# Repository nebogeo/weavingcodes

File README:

Collected code for the weavingcodes/codingweaves project.

http://kairotic.org

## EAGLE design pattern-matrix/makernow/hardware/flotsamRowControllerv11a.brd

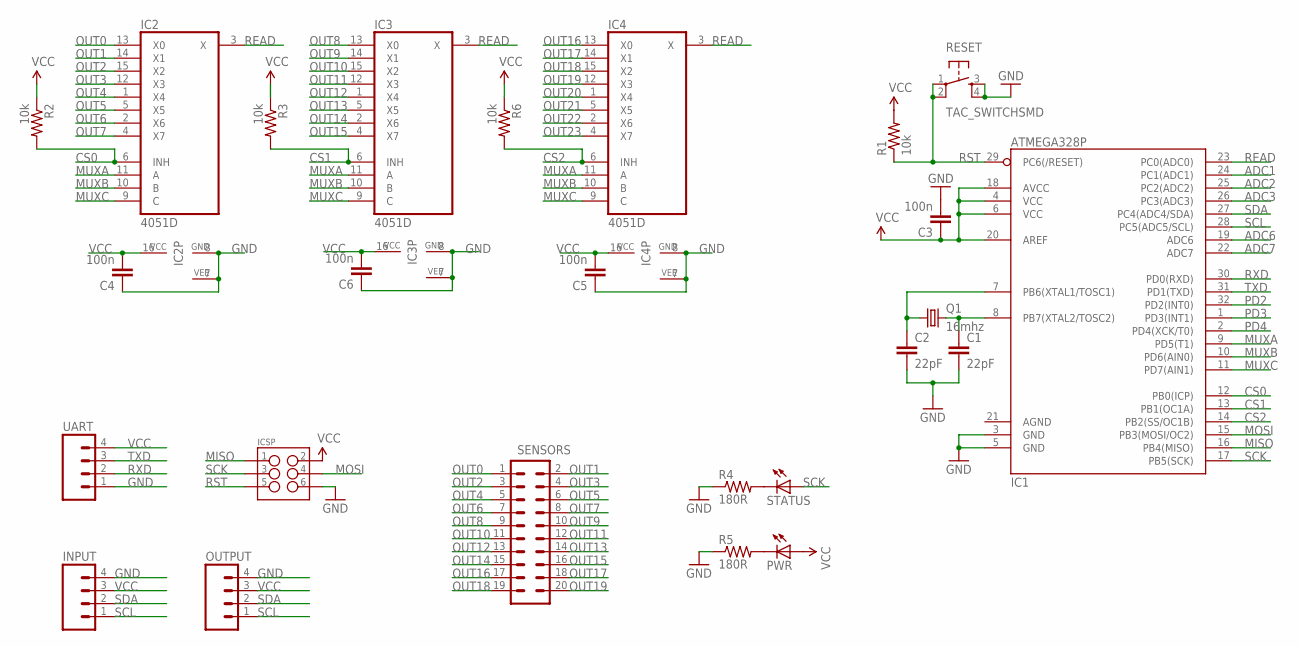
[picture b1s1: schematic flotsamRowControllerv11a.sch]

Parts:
C1, C2: 22pF; 0805
C3, C4, C5, C6: 100n; 0805
IC1: ATMEGA328P; TQFP32-08
IC2, IC3, IC4: 4051D; SO16
ICSP: M03X2FEMALE; 2X3
INPUT: M04LOCK; 1X04_LOCK
OUTPUT: M04LOCK; 1X04_LOCK
PWR: LEDSML0805; SML0805
Q1: 16mhz; HC49UP
R1, R2, R3, R6: 10k; 0805
R4, R5: 180R; 0805
RESET: TAC_SWITCHSMD; TACTILE-SWITCH-SMD
SENSORS: M10X22X10_LOCK; 2X10_LOCK
STATUS: LEDSML0805; SML0805
UART: M04LOCK; 1X04_LOCK

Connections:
ADC1: IC1.24 (PC1(ADC1))
ADC2: IC1.25 (PC2(ADC2))
ADC3: IC1.26 (PC3(ADC3))
ADC6: IC1.19 (ADC6)
ADC7: IC1.22 (ADC7)
CS0: IC1.12 (PB0(ICP)), IC2.6 (INH), R2.2
CS1: IC1.13 (PB1(OC1A)), IC3.6 (INH), R3.2
CS2: IC1.14 (PB2(SS/OC1B)), IC4.6 (INH), R6.2
GND: C1.2, C2.2, C3.2, C4.1, C5.1, C6.1, IC1.3 (GND), IC1.5 (GND), IC2.7 (VEE), IC2.8 (GND), IC3.7 (VEE), IC3.8 (GND), IC4.7 (VEE), IC4.8 (GND), ICSP.6, INPUT.4, OUTPUT.4, R4.1, R5.1, RESET.3, RESET.4, UART.1
MISO: IC1.16 (PB4(MISO)), ICSP.1
MOSI: IC1.15 (PB3(MOSI/OC2)), ICSP.4
MUXA: IC1.9 (PD5(T1)), IC2.11 (A), IC3.11 (A), IC4.11 (A)
MUXB: IC1.10 (PD6(AIN0)), IC2.10 (B), IC3.10 (B), IC4.10 (B)
MUXC: IC1.11 (PD7(AIN1)), IC2.9 (C), IC3.9 (C), IC4.9 (C)
unnamed: C1.1, IC1.8 (PB7(XTAL2/TOSC2)), Q1.2
unnamed: C2.1, IC1.7 (PB6(XTAL1/TOSC1)), Q1.1
unnamed: PWR.C, R5.2
unnamed: R4.2, STATUS.C
OUT0: IC2.13 (X0), SENSORS.1
OUT1: IC2.14 (X1), SENSORS.2
OUT2: IC2.15 (X2), SENSORS.3
OUT3: IC2.12 (X3), SENSORS.4
OUT4: IC2.1 (X4), SENSORS.5
OUT5: IC2.5 (X5), SENSORS.6
OUT6: IC2.2 (X6), SENSORS.7
OUT7: IC2.4 (X7), SENSORS.8
OUT8: IC3.13 (X0), SENSORS.9
OUT9: IC3.14 (X1), SENSORS.10
OUT10: IC3.15 (X2), SENSORS.11
OUT11: IC3.12 (X3), SENSORS.12
OUT12: IC3.1 (X4), SENSORS.13
OUT13: IC3.5 (X5), SENSORS.14
OUT14: IC3.2 (X6), SENSORS.15
OUT15: IC3.4 (X7), SENSORS.16
OUT16: IC4.13 (X0), SENSORS.17
OUT17: IC4.14 (X1), SENSORS.18
OUT18: IC4.15 (X2), SENSORS.19
OUT19: IC4.12 (X3), SENSORS.20
OUT20: IC4.1 (X4)
OUT21: IC4.5 (X5)
OUT22: IC4.2 (X6)
OUT23: IC4.4 (X7)
PD2: IC1.32 (PD2(INT0))
PD3: IC1.1 (PD3(INT1))
PD4: IC1.2 (PD4(XCK/T0))
READ: IC1.23 (PC0(ADC0)), IC2.3 (X), IC3.3 (X), IC4.3 (X)
RST: IC1.29 (PC6(/RESET)), ICSP.5, R1.1, RESET.1, RESET.2
RXD: IC1.30 (PD0(RXD)), UART.2
SCK: IC1.17 (PB5(SCK)), ICSP.3, STATUS.A
SCL: IC1.28 (PC5(ADC5/SCL)), INPUT.1, OUTPUT.1
SDA: IC1.27 (PC4(ADC4/SDA)), INPUT.2, OUTPUT.2
TXD: IC1.31 (PD1(TXD)), UART.3
VCC: C3.1, C4.2, C5.2, C6.2, IC1.4 (VCC), IC1.6 (VCC), IC1.18 (AVCC), IC1.20 (AREF), IC2.16 (VCC), IC3.16 (VCC), IC4.16 (VCC), ICSP.2, INPUT.3, OUTPUT.3, PWR.A, R1.2, R2.1, R3.1, R6.1, UART.4

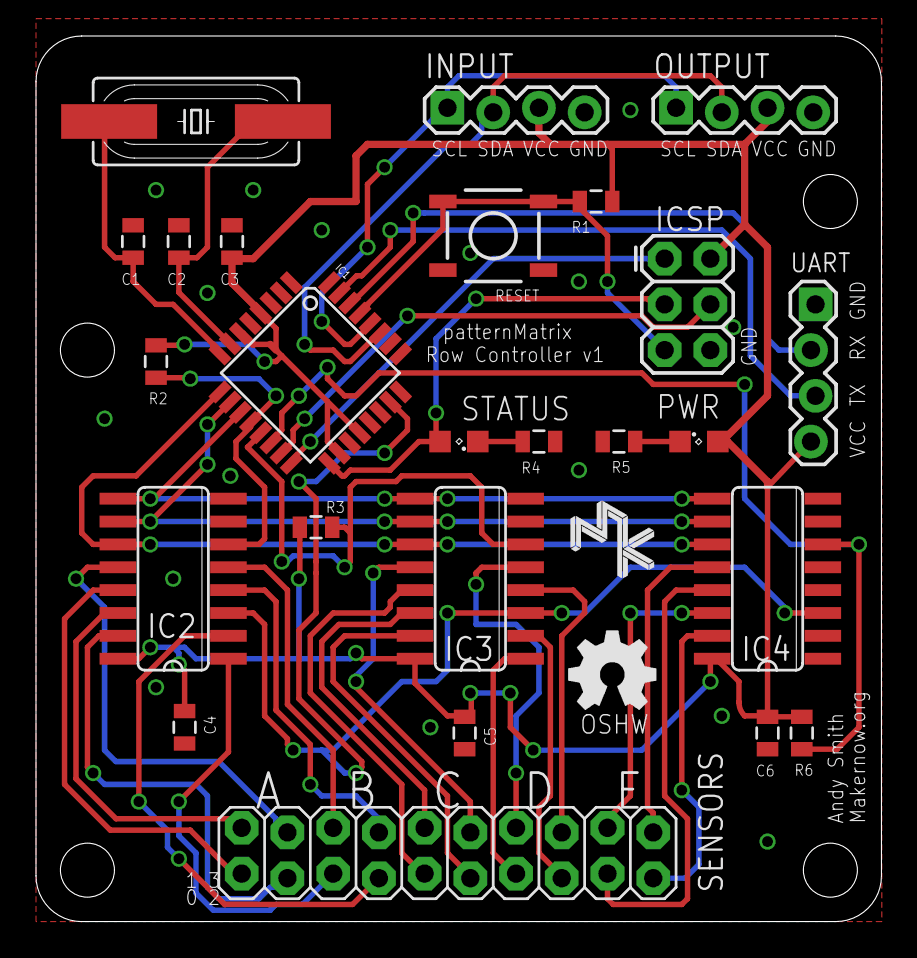
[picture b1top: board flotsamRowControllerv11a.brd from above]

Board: 2 copper layers, 47.0 x 49.2 mm, 27 parts (0 on the bottom side), 41 nets.

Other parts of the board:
U$1: MK_5MM
U$2: OSHW_5MM

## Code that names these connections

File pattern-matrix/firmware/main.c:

// Copyright (C) 2015 Dave Griffiths
//
// This program is free software; you can redistribute it and/or modify
// it under the terms of the GNU General Public License as published by
// the Free Software Foundation; either version 2 of the License, or
// (at your option) any later version.
//
// This program is distributed in the hope that it will be useful,
// but WITHOUT ANY WARRANTY; without even the implied warranty of
// MERCHANTABILITY or FITNESS FOR A PARTICULAR PURPOSE.  See the
// GNU General Public License for more details.
//
// You should have received a copy of the GNU General Public License
// along with this program; if not, write to the Free Software
// Foundation, Inc., 59 Temple Place - Suite 330, Boston, MA 02111-1307, USA.

// pattern matrix avr firmware
// reads the sensor data and makes it accessible to i2c devices

#include <avr/io.h>
#include <util/delay.h>
#include <stdlib.h>
#include <avr/interrupt.h>

#include "I2C_slave.h"

// buffer used to convert integer to string
char buffer[3];

#define LED PB0

#define PIN_READ PC0
#define PIN_MUXA PD5
#define PIN_MUXB PD6
#define PIN_MUXC PD7
#define PIN_CS0 PB0
#define PIN_CS1 PB1
#define PIN_CS2 PB2
#define PIN_STATUS PB5

//#define SINGLE_SENSOR
#define I2C_ID 0x36

// 35
// 33
// 34
// 32
// 36

void set_led_state(unsigned char s)
{
    if (s) PORTB|=_BV(PIN_STATUS);
    else PORTB&=~_BV(PIN_STATUS);
}

void outputb(unsigned int pin, unsigned char s)
{
    if (s) PORTB|=_BV(pin);
    else PORTB&=~_BV(pin);
}

void outputd(unsigned int pin, unsigned char s)
{
    if (s) PORTD|=_BV(pin);
    else PORTD&=~_BV(pin);
}

void index_sensor(unsigned int i) {
  unsigned int bank=i/8;
  unsigned int sensor=i%8;

  PORTD=((sensor&0x07)<<5);

  // set bits
  PORTB|=0x07;
  if (bank==0) outputb(PIN_CS0, 0);
  else if (bank==1) outputb(PIN_CS1, 0);
  else outputb(PIN_CS2, 0);
}

#define cbi(sfr, bit) (_SFR_BYTE(sfr) &= ~_BV(bit))

int main(void){
  	I2C_init(I2C_ID<<1); // initalize as slave with address 0x32

	// allow interrupts
        sei();

        // setup outputs
        DDRB = 0x00;
        DDRB |= _BV( PIN_STATUS );
        DDRB |= _BV( PIN_CS0 );
        DDRB |= _BV( PIN_CS1 );
        DDRB |= _BV( PIN_CS2 );

        DDRD = 0x00;
        DDRD |= _BV( PIN_MUXA );
        DDRD |= _BV( PIN_MUXB );
        DDRD |= _BV( PIN_MUXC );

        DDRC = 0x00;

        outputd(PIN_MUXA, 0);
        outputd(PIN_MUXB, 0);
        outputd(PIN_MUXC, 0);
        outputb(PIN_CS0, 0);
        outputb(PIN_CS1, 1);
        outputb(PIN_CS2, 1);

        for (int i=0; i<0xFF; i++) {
          i2cbuffer[i]=99;
        }

        int sensor = 1;
        int i2c_index = 0;

	while(1) {

#ifdef SINGLE_SENSOR

          _delay_ms(500);
          outputb(PIN_STATUS, 0);
          PORTD=((sensor&0x07)<<5);
          _delay_ms(100);
          if (PINC&_BV(PIN_READ)) {
            if (i2cbuffer[sensor]==1) outputb(PIN_STATUS, 1);
            i2cbuffer[sensor]=0;
          } else {
            if (i2cbuffer[sensor]==0) outputb(PIN_STATUS, 1);
            i2cbuffer[sensor]=1;
          }

          sensor++;
          if (sensor>4) sensor=0;

#else // 4 sensors

          _delay_ms(50);
          outputb(PIN_STATUS, 0);

          index_sensor(sensor);

          _delay_ms(10);
          if (PINC&_BV(PIN_READ)) {
            if (i2cbuffer[i2c_index]==1) outputb(PIN_STATUS, 1);
            i2cbuffer[i2c_index]=0;
          } else {
            if (i2cbuffer[i2c_index]==0) outputb(PIN_STATUS, 1);
            i2cbuffer[i2c_index]=1;
          }

          i2c_index++;
          sensor++;
          if (sensor>20) {
            sensor=0;
            i2c_index=0;
          }

#endif


	}

	return 0;
}

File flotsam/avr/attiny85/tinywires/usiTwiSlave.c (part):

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#  define DDR_USI             DDRB
#  define PORT_USI            PORTB
#  define PIN_USI             PINB
#  define PORT_USI_SDA        PB5
#  define PORT_USI_SCL        PB7
#  define PIN_USI_SDA         PINB5
#  define PIN_USI_SCL         PINB7
#  define USI_START_COND_INT  USISIF
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#  define DDR_USI             DDRB
#  define PORT_USI            PORTB
#  define PIN_USI             PINB
#  define PORT_USI_SDA        PB0
#  define PORT_USI_SCL        PB2
#  define PIN_USI_SDA         PINB0
#  define PIN_USI_SCL         PINB2
#  define USI_START_COND_INT  USISIF
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#  define DDR_USI             DDRB
#  define PORT_USI            PORTB
#  define PIN_USI             PINB
#  define PORT_USI_SDA        PB0
#  define PORT_USI_SCL        PB2
#  define PIN_USI_SDA         PINB0
#  define PIN_USI_SCL         PINB2
#  define USI_START_COND_INT  USISIF
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#  define DDR_USI             DDRB
#  define PORT_USI            PORTB
#  define PIN_USI             PINB
#  define PORT_USI_SDA        PB0
#  define PORT_USI_SCL        PB2
#  define PIN_USI_SDA         PINB0
#  define PIN_USI_SCL         PINB2
#  define USI_START_COND_INT  USISIF
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ISR( USI_START_VECTOR )
{

    PORTB|=_BV(PB3);


  /*
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
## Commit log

2014-10-17 added readme
2014-10-17 fixes for possible demo
2014-10-27 added online version
2014-10-27 added comments
2014-11-06 meander
2014-11-06 missing files
2014-11-12 better lsystem and stuff for flotsam
2014-11-25 added attiny85 code
2014-11-25 shifting stuff
2014-11-25 added atmega code
2014-11-25 removed cruft
2014-11-25 tidy
2014-11-26 rpi -> atmega works!
2014-11-26 attiny forgotten bits
2014-11-27 fixed reading -> pi
2014-12-28 added tablet weaving/livecoding sketch
2014-12-29 tablet weaving stuff
2015-01-02 added card viz
2015-01-02 links to source
2015-01-04 straight threads added to tablet
2015-02-12 added pattern matrix stuff
2015-02-12 gpio/osc/jellyfish comms
2015-02-27 tablet enlargement
2015-04-12 stuff for pattern matrix hardware
2015-04-12 sorting out pattern matrix code
2015-04-13 added python i2c code
2015-04-13 structure pygame hack
2015-04-17 firmware updated
2015-04-19 multisensor version added
2015-04-19 new wwloomsim
2015-04-19 added pattern cascade driver
2015-04-19 driver updates, untested
2015-04-19 temp
2015-04-22 colour and weave experiment, broken
2015-05-04 multiyarn and refactor
2015-05-04 double loom
2015-05-07 munich day 2
2015-05-07 draft modulo probs fixed
2015-05-07 selvedge smoothing
2015-05-07 final fiddly bits, thursday munich
2015-05-08 stuff from munich friday
2015-05-11 tidal residues
2015-05-11 types
2015-05-11 work not in progress
2015-05-11 lasercuttings etc
2015-06-02 added sound thingy for miners court
2015-06-02 miners court bits
2015-06-09 added thread tex
2015-06-09 added new colour seqs
2015-06-15 AIR/sheffield changes
2015-06-15 added missing munich files
2015-07-08 stuff for installations...
2015-07-20 added qt interface
2015-07-20 styling and adding colour
2015-07-20 connected up colours
2015-07-20 added livecoding editor
2015-07-21 paths fixes for osx
2015-07-21 added notes etc
2015-07-21 install fiddling
2015-07-21 start up state better
2015-07-21 mac install messing
2015-07-21 fixed warp draft addr
2015-10-15 dabblings with purescript
2015-10-19 further attempts at porting
2015-10-22 start of diagrams support
2015-10-27 dance weaving
2015-10-31 toothpaste added
2015-11-08 toothpaste updates
2015-11-23 added colour codes to dyadic
2015-11-23 missing images
2015-11-23 default loom to tabby weave
2016-01-25 added colour and setup commands to the tablet sim language
2016-01-25 colour flip
2016-01-25 added images
2017-05-14 mainly changes for munich installation, penelope project
2018-10-31 changes for new penelope version
2018-11-01 added thread texture

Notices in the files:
parts and their libraries:
SparkFun-Connectors: Licensing: Creative Commons ShareAlike 4.0 International - https://creativecommons.org/licenses/by-sa/4.0
